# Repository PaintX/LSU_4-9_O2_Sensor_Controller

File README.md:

# LSU_4-9_O2_Sensor_Controller
Controlleur pour sonde lambda LSU 4.9 avec arduino

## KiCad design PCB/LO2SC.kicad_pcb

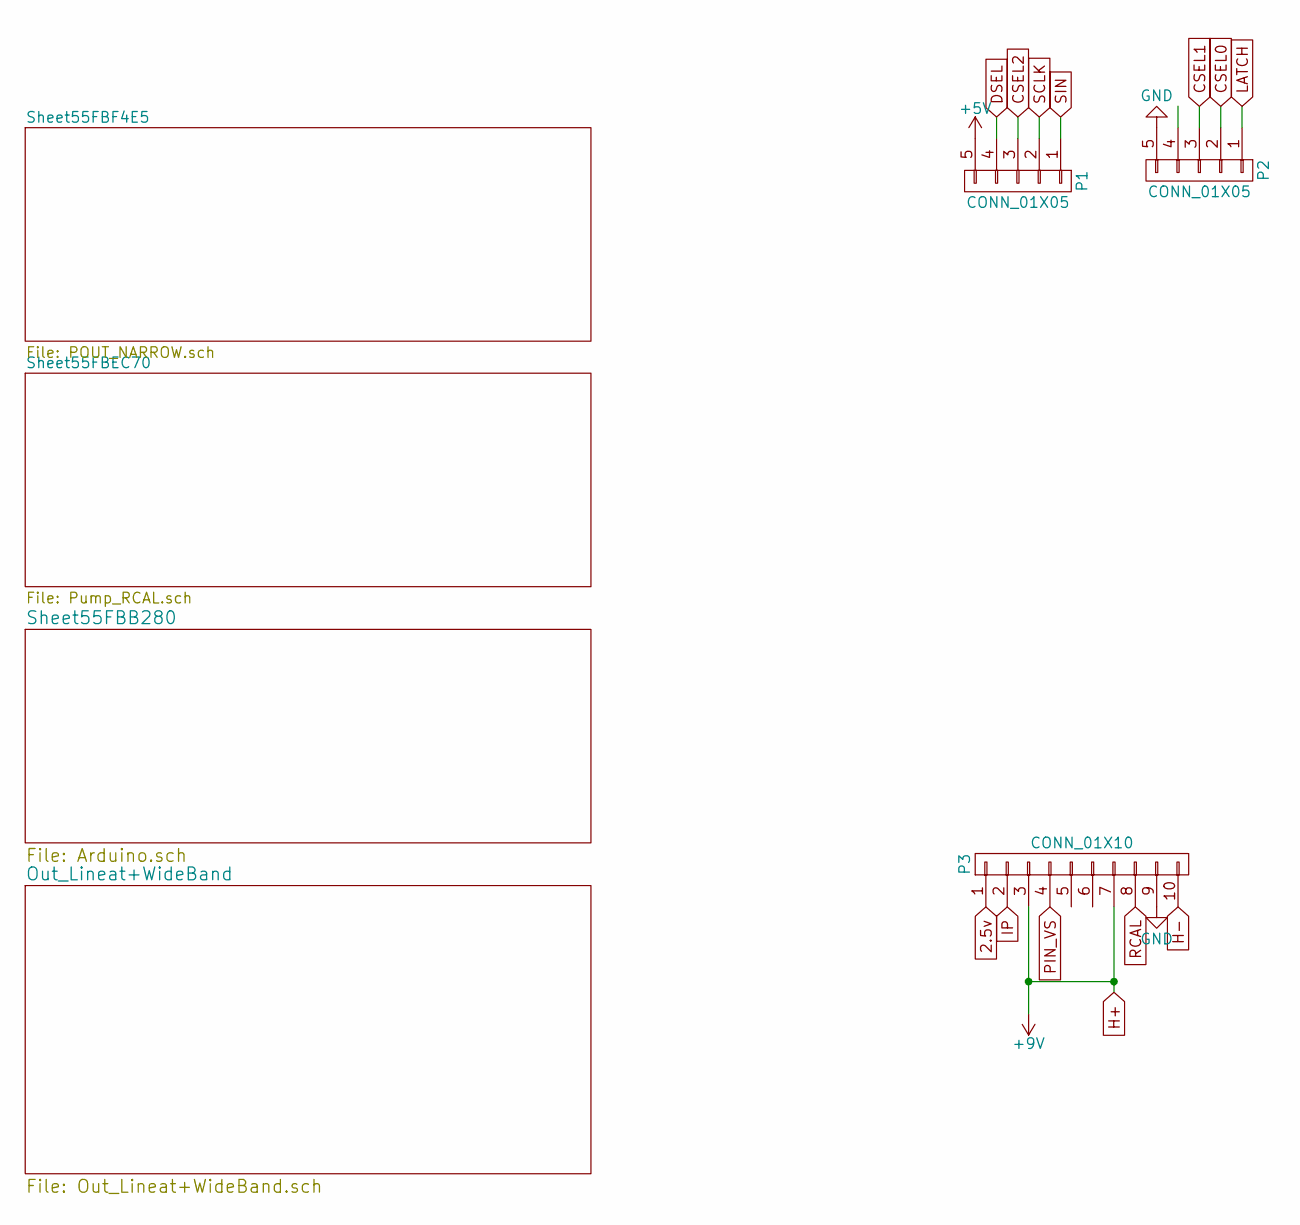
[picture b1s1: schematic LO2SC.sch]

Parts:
P1, P2: CONN_01X05; Pin_Header_Straight_1x05
P3: CONN_01X10; JAE_10Pins

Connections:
2.5v: P3.1; also elsewhere on the board
+5V: P1.5; also elsewhere on the board
CSEL0: P2.2; also elsewhere on the board
CSEL1: P2.3; also elsewhere on the board
CSEL2: P1.3; also elsewhere on the board
DSEL: P1.4; also elsewhere on the board
GND: P2.5, P3.9; also elsewhere on the board
H+: P3.3, P3.7
IP: P3.2; also elsewhere on the board
LATCH: P2.1; also elsewhere on the board
PIN_VS: P3.4; also elsewhere on the board
RCAL: P3.8; also elsewhere on the board
SCLK: P1.2; also elsewhere on the board
SIN: P1.1; also elsewhere on the board

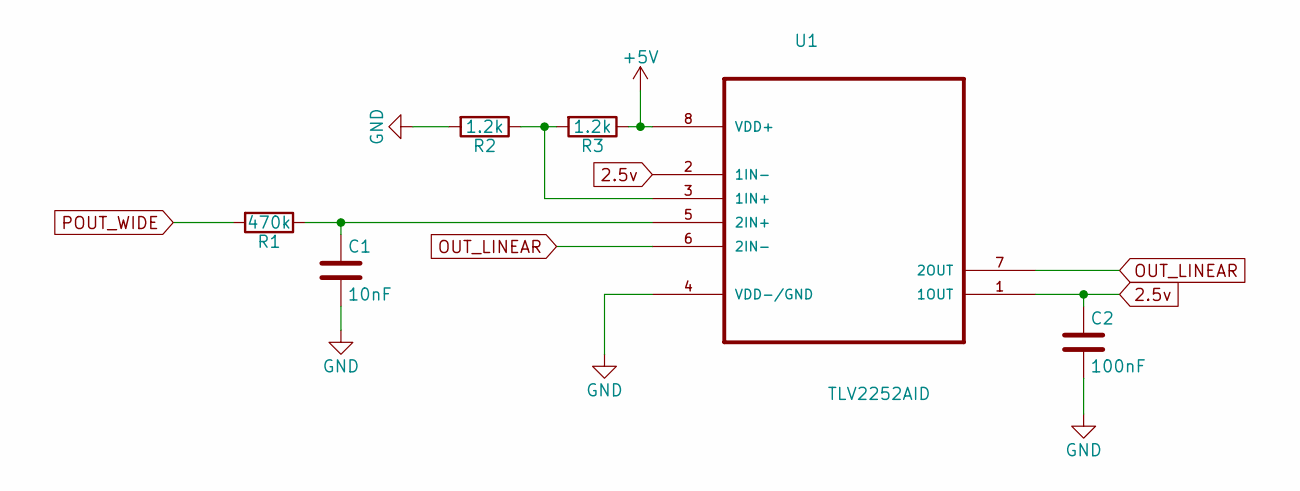
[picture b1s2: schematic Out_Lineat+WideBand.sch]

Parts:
C1: 10nF; C_0603_HandSoldering
C2: 100nF; C_0603_HandSoldering
R1: 470k; R_0603_HandSoldering
R2, R3: 1.2k; R_0603_HandSoldering
U1: TLV2252AID; SOIC127P600X175-8N

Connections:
2.5v: C2.1, U1.1 (1OUT), U1.2 (1IN-); also elsewhere on the board
+5V: R3.1, U1.8 (VDD+); also elsewhere on the board
GND: C1.2, C2.2, R2.2, U1.4 (VDD-/GND); also elsewhere on the board
unnamed: C1.1, R1.1, U1.5 (2IN+)
unnamed: R2.1, R3.2, U1.3 (1IN+)
OUT_LINEAR: U1.6 (2IN-), U1.7 (2OUT)
POUT_WIDE: R1.2; also elsewhere on the board

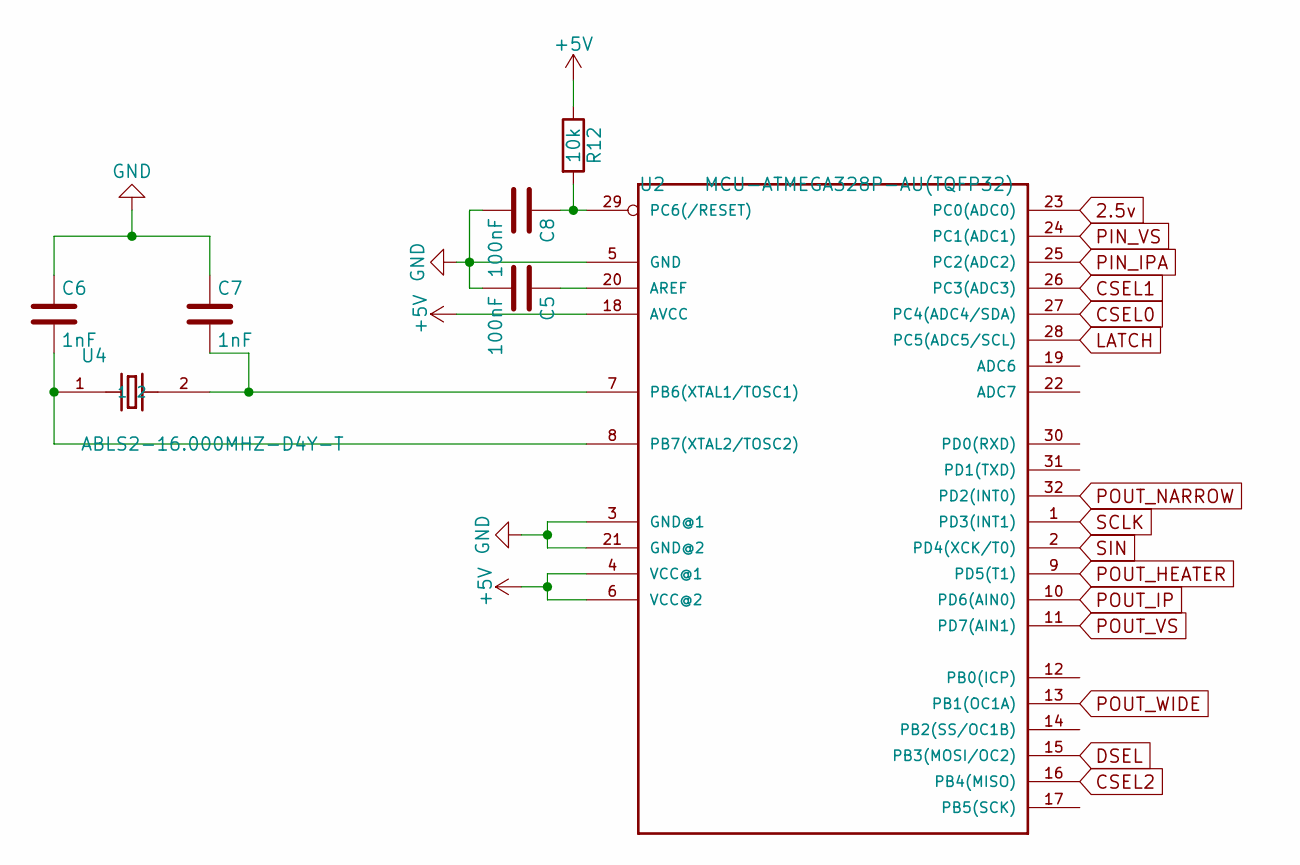
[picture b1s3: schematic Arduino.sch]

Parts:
C5, C8: 100nF; C_0603_HandSoldering
C6, C7: 1nF; C_0603_HandSoldering
R12: 10k; R_0603_HandSoldering
U2: MCU-ATMEGA328P-AU(TQFP32); TQFP32-0.8-7X7MM
U4: ABLS2-16.000MHZ-D4Y-T; HC-49

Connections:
2.5v: U2.23 (PC0(ADC0)); also elsewhere on the board
+5V: R12.1, U2.4 (VCC@1), U2.6 (VCC@2), U2.18 (AVCC); also elsewhere on the board
CSEL0: U2.27 (PC4(ADC4/SDA)); also elsewhere on the board
CSEL1: U2.26 (PC3(ADC3)); also elsewhere on the board
CSEL2: U2.16 (PB4(MISO)); also elsewhere on the board
DSEL: U2.15 (PB3(MOSI/OC2)); also elsewhere on the board
GND: C5.2, C6.1, C7.1, C8.2, U2.3 (GND@1), U2.5 (GND), U2.21 (GND@2); also elsewhere on the board
LATCH: U2.28 (PC5(ADC5/SCL)); also elsewhere on the board
unnamed: C5.1, U2.20 (AREF)
unnamed: C6.2, U2.8 (PB7(XTAL2/TOSC2)), U4.1
unnamed: C7.2, U2.7 (PB6(XTAL1/TOSC1)), U4.2
unnamed: C8.1, R12.2, U2.29 (PC6(/RESET))
PIN_IPA: U2.25 (PC2(ADC2)); also elsewhere on the board
PIN_VS: U2.24 (PC1(ADC1)); also elsewhere on the board
POUT_IP: U2.10 (PD6(AIN0)); also elsewhere on the board
POUT_NARROW: U2.32 (PD2(INT0)); also elsewhere on the board
POUT_VS: U2.11 (PD7(AIN1)); also elsewhere on the board
POUT_WIDE: U2.13 (PB1(OC1A)); also elsewhere on the board
SCLK: U2.1 (PD3(INT1)); also elsewhere on the board
SIN: U2.2 (PD4(XCK/T0)); also elsewhere on the board

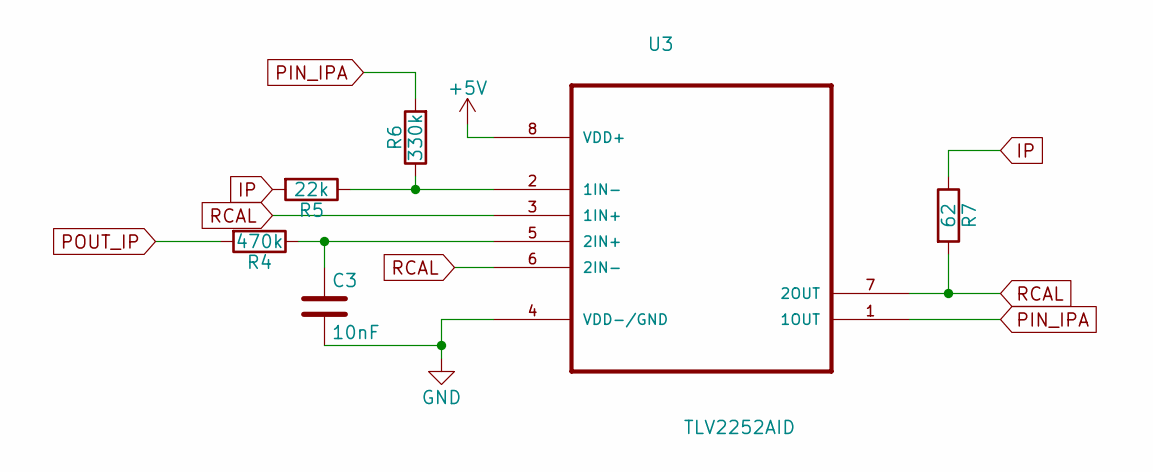
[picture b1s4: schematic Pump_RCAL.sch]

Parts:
C3: 10nF; C_0603_HandSoldering
R4: 470k; R_0603_HandSoldering
R5: 22k; R_0603_HandSoldering
R6: 330k; R_0603_HandSoldering
R7: 62; R_0603_HandSoldering
U3: TLV2252AID; SOIC127P600X175-8N

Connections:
+5V: U3.8 (VDD+); also elsewhere on the board
GND: C3.2, U3.4 (VDD-/GND); also elsewhere on the board
IP: R5.2, R7.1; also elsewhere on the board
unnamed: C3.1, R4.1, U3.5 (2IN+)
unnamed: R5.1, R6.1, U3.2 (1IN-)
PIN_IPA: R6.2, U3.1 (1OUT); also elsewhere on the board
POUT_IP: R4.2; also elsewhere on the board
RCAL: R7.2, U3.3 (1IN+), U3.6 (2IN-), U3.7 (2OUT); also elsewhere on the board

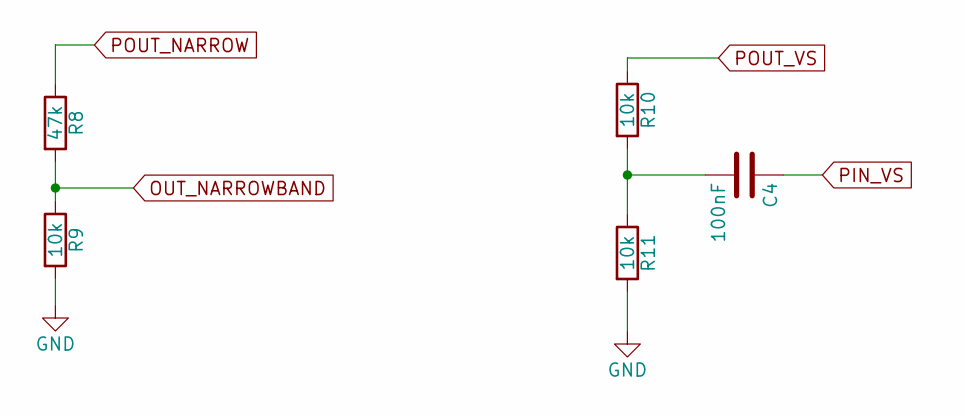
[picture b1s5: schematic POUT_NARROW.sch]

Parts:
C4: 100nF; C_0603_HandSoldering
R8: 47k; R_0603_HandSoldering
R9, R10, R11: 10k; R_0603_HandSoldering

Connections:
GND: R9.2, R11.2; also elsewhere on the board
unnamed: C4.2, R10.2, R11.1
OUT_NARROWBAND: R8.2, R9.1
PIN_VS: C4.1; also elsewhere on the board
POUT_NARROW: R8.1; also elsewhere on the board
POUT_VS: R10.1; also elsewhere on the board

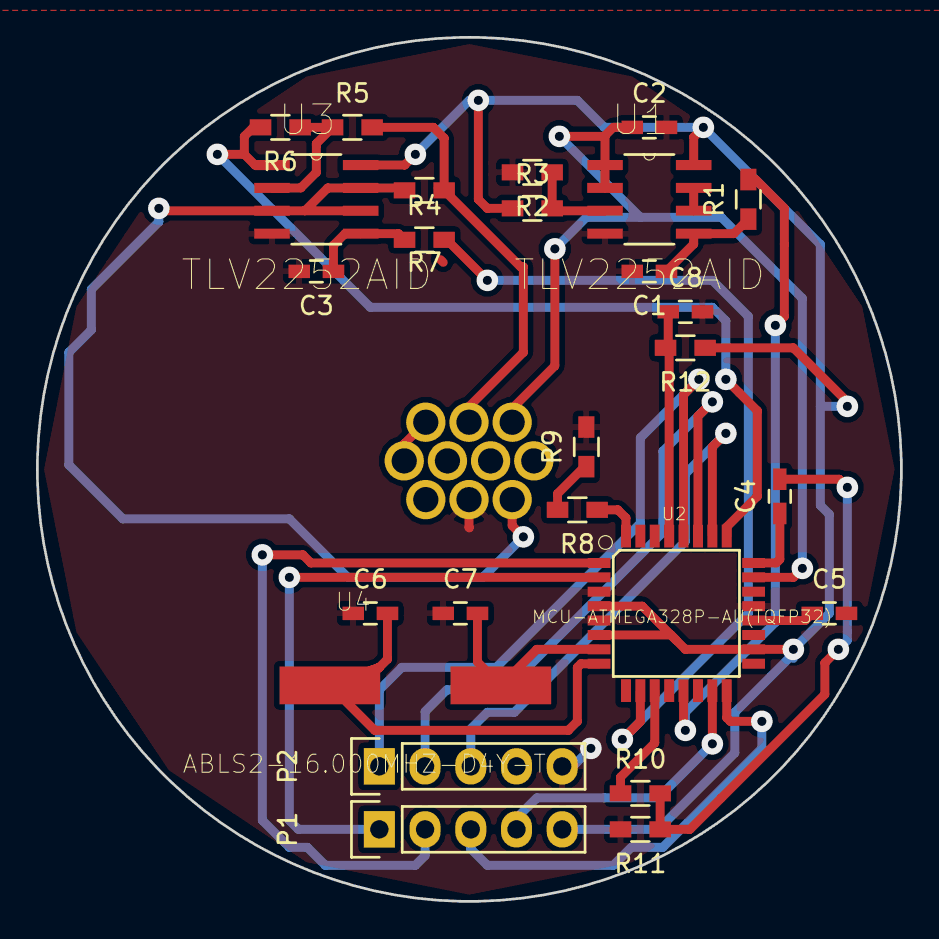
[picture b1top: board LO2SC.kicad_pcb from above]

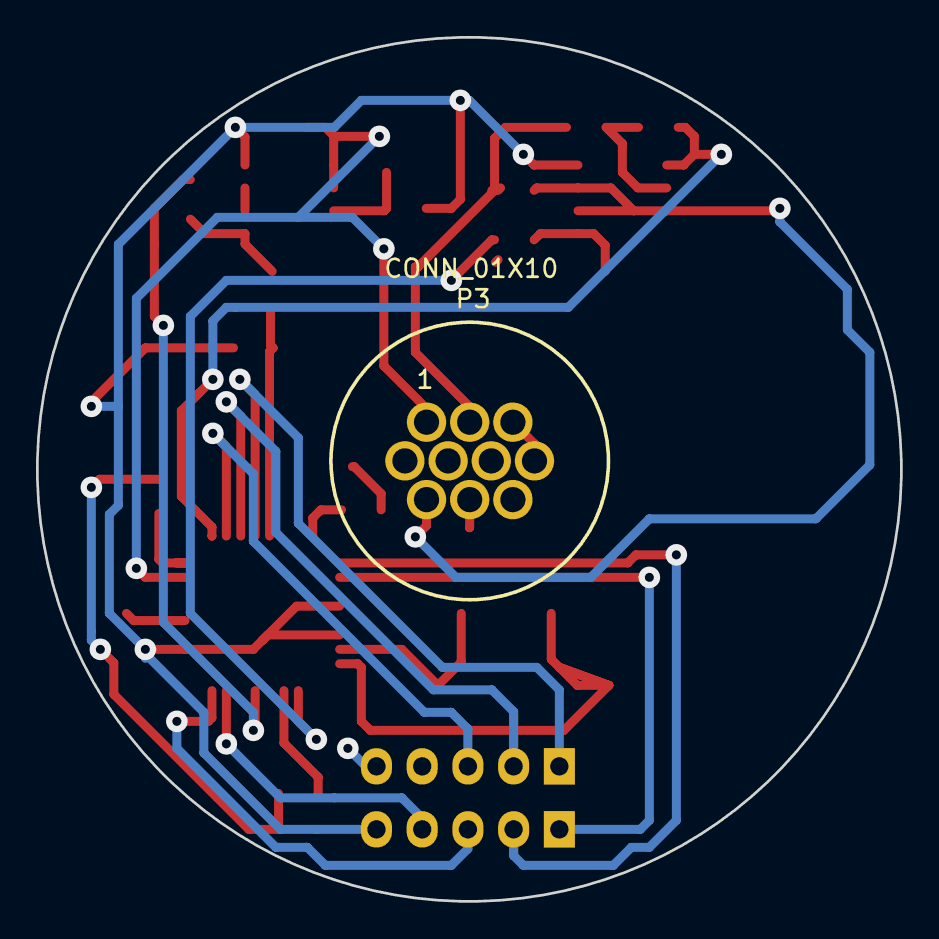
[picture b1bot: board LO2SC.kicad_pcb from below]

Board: 2 copper layers, 48.0 x 48.0 mm, 28 parts (2 on the bottom side), 30 nets.

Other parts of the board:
Ref**: Val**; vue3D

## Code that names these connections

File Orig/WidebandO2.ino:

#include <RunningAverage.h>
#include <PID_v1.h>



/*
 Some configurations
*/


#define BOARD_UNO


const float targetLambda = 1.0; // Narrowband simulation, cross point in lambda
const float widebandTop = 2.0; // Where the +5v of the linear wideband output is

const int warmUpDelay = 20000; // Initial delay we wait before starting heating of the sensor, in millis
const int initialRampUpTill = 255 / 14.0 * 7.5; // Heater warm up stage, this sets the top (TODO: Measure input voltage, max output should be 7.5v)
const int initialRampUpStep = 255 / (14.0 / 0.5); // Heater warm up stage, this is how fast the voltage ramps up per second, spec sheet says .5v a second).

double heatTarget = 2.3 / 1300.0 * 200.0; // Target voltage, this is pulse voltage divided by total target resistance, times the target cell resistance
int heatSampleTime = 500; // How often the heater is sampled for PID, in milliseconds
double pumpTarget = 0.45; // Target Nernst cell voltage
int pumpSampleTime = 40; // How often the nernst cell is sampled for PID, in milliseconds (should be slower than the RC filter feeding the opamp)

int speedOfLoop = 4; // How many millis it takes for loop to run, on Teensy++ 2.0, it's 4 millis

#define DEBUG       // DEBUG enables human readable logging and info messages
#define NO_SERIAL   // NO_SERIAL disables the CSV output of the controllers controls, a nice way to view this log is with OpenLogViewer - http://olv.diyefi.org/



/*
  Pin Definitions
*/
#if defined(BOARD_TEENSYPP20)
// Inputs
const int PIN_VGND = PIN_F0; // Analog In - Level of the virtual ground
const int PIN_VS = PIN_F1; // Analog In - Reads Nernst Cell voltage
const int PIN_IPA = PIN_F2; // Analog In - Measures pump current via differential amp

// Sensor control
const int POUT_VS = PIN_B6; // Digital Out - Pulses Nernst Cell to calculate internal resistance
const int POUT_HEATER = PIN_B5; // Analog Out - Heater control, keeps Nernst cell at right temperature
const int POUT_IP = PIN_B4; // Analog Out - Pump cell current output, keeps Nernst cell in stoich range

// Outputs
const int POUT_NARROW = PIN_D0; // Digital Out - Feeds voltage divider, 0-1v signal to ECU
const int POUT_WIDE = PIN_D1; // Analog Out - Wideband linear output



#elif defined(BOARD_UNO)
const int PIN_VGND = A0; // Analog In - Level of the virtual ground
const int PIN_VS = A1; // Analog In - Reads Nernst Cell voltage
const int PIN_IPA = A2; // Analog In - Measures pump current via differential amp

// Sensor control
const int POUT_VS = 7; // Digital Out - Pulses Nernst Cell to calculate internal resistance
const int POUT_HEATER = 5; // Analog Out - Heater control, keeps Nernst cell at right temperature
const int POUT_IP = 6; // Analog Out - Pump cell current output, keeps Nernst cell in stoich range

// Outputs
const int POUT_NARROW = 2; // Digital Out - Feeds voltage divider, 0-1v signal to ECU
const int POUT_WIDE = 9; // Analog Out - Wideband linear output



#else
#error "No board defined"
#endif

/*
  Start of code
*/
#ifdef DEBUG
#define DP(...) Serial.print(__VA_ARGS__)
#define DPL(...) Serial.println(__VA_ARGS__)
#else
#define DP(...)
#define DPL(...)
#endif



double heatIn, heatOut;
PID heater(&heatIn, &heatOut, &heatTarget, 800, 100, 1, REVERSE);
double pumpIn, pumpOut;
PID pump(&pumpIn, &pumpOut, &pumpTarget, 800, 100, 0.001, DIRECT);

RunningAverage vgndavg(1);
RunningAverage ipaavg(pumpSampleTime/speedOfLoop*5);
RunningAverage nernstavg(pumpSampleTime/speedOfLoop);

float volts(int adc) {
  return adc / 1024.0 * 5.0;
}

float vGndVolts() {
  vgndavg.addValue(volts(analogRead(PIN_VGND)));
  return vgndavg.getAverage();
}

float nernstVolts() {
  nernstavg.addValue(volts(analogRead(PIN_VS)));
  return nernstavg.getAverage();
}

float pumpVolts() {
  ipaavg.addValue(volts(analogRead(PIN_IPA)));
  return ipaavg.getAverage();
}

float nernstResistanceVolts() {
    int before = analogRead(PIN_VS); // Read nernst before pulse
    digitalWrite(POUT_VS, 1); // Pulse it
    delayMicroseconds(30); // Wait for the pulse cap to reach full voltage
    int after = analogRead(PIN_VS); // Read during the pulse
    digitalWrite(POUT_VS, 0); // Restore it
    delayMicroseconds(200); // Give the nernst cell and cap some time to equalise back out after
    return volts(after - before);
}

#define LAMBDA_LOOKUP_SIZE 20
const float lambdaLookup[LAMBDA_LOOKUP_SIZE] = {
  -2.22, 0.65,
  -1.82, 0.70,
  -1.11, 0.80,
  -0.50, 0.90,
   0.00, 1.016,
   0.33, 1.18,
   0.67, 1.43,
   0.94, 1.70,
   1.38, 2.42,
   2.54, 4.99
};

float lambda(float amps) {
  if (amps < lambdaLookup[0]) return 0.0; // Too rich for sensor
  if (amps > lambdaLookup[LAMBDA_LOOKUP_SIZE-2]) return 9.99; // To lean to care
  for (int x = 0; x < LAMBDA_LOOKUP_SIZE-2; x = x + 2) {
    if (amps >= lambdaLookup[x] && amps <= lambdaLookup[x+2]) {
      // Interpolate the lookup
      return (amps - lambdaLookup[x]) / (lambdaLookup[x+2] - lambdaLookup[x]) * (lambdaLookup[x+3] - lambdaLookup[x+1]) + lambdaLookup[x+1];
    }
  }
}

void serialHeader() {
  #ifndef NO_SERIAL
  Serial.println("millis,lambda,ipa,vgnd,heatIn,heatOut,heatTarget,pumpIn,pumpOut,pumpTarget");
  #endif
}

void serialLog(float l, float ipa, float vgnd) {
  // lambda, ipa, vgnd, heatIn, heatOut, heatTarget, pumpIn, pumpOut, pumpTarget
  #ifndef DEBUG
  #ifndef NO_SERIAL
    Serial.print(millis());
    Serial.print(",");
    Serial.print(l);
    Serial.print(",");
    Serial.print(ipa);
    Serial.print(",");
    Serial.print(vgnd);
    Serial.print(",");
    Serial.print(heatIn);
    Serial.print(",");
    Serial.print(heatOut);
    Serial.print(",");
    Serial.print(heatTarget);
    Serial.print(",");
    Serial.print(pumpIn);
    Serial.print(",");
    Serial.print(pumpOut);
    Serial.print(",");
    Serial.print(pumpTarget);
    Serial.println("");
  #endif
  #endif
}

void setup() {
  // Configure pins
  pinMode(PIN_VS, INPUT);
  pinMode(PIN_IPA, INPUT);
  pinMode(PIN_VGND, INPUT);
  
  pinMode(POUT_NARROW, OUTPUT);
  digitalWrite(POUT_NARROW, 0);
  
  pinMode(POUT_WIDE, OUTPUT);
  analogWrite(POUT_WIDE, 0);
  
  pinMode(POUT_VS, OUTPUT);
  digitalWrite(POUT_VS, 0);
  
  pinMode(POUT_IP, OUTPUT);
  analogWrite(POUT_IP, 128);
  
  pinMode(POUT_HEATER, OUTPUT);
  analogWrite(POUT_HEATER, 0);
  
  // Configure PIDs
  heater.SetOutputLimits(0, initialRampUpTill);
  heater.SetSampleTime(heatSampleTime);
  heater.SetMode(AUTOMATIC);
  pump.SetOutputLimits(0, 250);
  pump.SetSampleTime(pumpSampleTime);
  pump.SetMode(AUTOMATIC);
  
  // Start running
  Serial.begin(115200);
  delay(1000);
  Serial.println();
  Serial.println();
  Serial.println();
  Serial.println();
  serialHeader();
  
  DPL("Hello Master!");
  
  DPL("Performing delay prior to warmup");
  delay(warmUpDelay); // Wait for some warm gasses through the exhaust
  
  // Slowly ramp up the sensors heater
  DPL("Warming up!");
  heatOut = 0;
  while (heatOut < initialRampUpTill) {
    if ((heatIn = nernstResistanceVolts()) < heatTarget) break; // Temperature is at target already, break out early to let PID take over
    heatOut += initialRampUpStep;
    analogWrite(POUT_HEATER, heatOut);
    serialLog(0.0,0.0,0.0);
    delay(1000);
  }
  DPL("Warm up complete");
}

#ifdef DEBUG
int debug;
#endif
void loop() {

  heatIn = nernstResistanceVolts();
  heater.Compute();
  analogWrite(POUT_HEATER, heatOut);
  
  float vgnd = vGndVolts();
  
  pumpIn = nernstVolts() - vgnd;
  pump.Compute();
  analogWrite(POUT_IP, pumpOut);
  
  // We rely on the circuit to give us a good range of mA to V, for a 61.9 ohm sense resistor, you need a 1 to 14.5395 ratio on the opamp, 22k and 330k across it gives a good result
  float ipa =  pumpVolts() - vgnd;
  float l = lambda(ipa);
  if (l > targetLambda) {
    digitalWrite(POUT_NARROW, 0); // Lean
  } else {
    digitalWrite(POUT_NARROW, 1); // Rich
  }
  
  unsigned int widebandOut;
  if (l < 0.65) widebandOut = 0;
  else if (l > widebandTop) widebandOut = 255;
  else widebandOut = ((l / widebandTop) - (0.65 / widebandTop)) * 255;
  analogWrite(POUT_WIDE, widebandOut);
  
  
  serialLog(l, ipa, vgnd);
  #ifdef DEBUG
  if (debug++ >= 500) {
    DP("Heater: Volts: "); DP(heatIn); DP(" Target: "); DP(heatTarget); DP(" Out: "); DPL(heatOut);
    DP("Nernst: Volts: "); DP(pumpIn); DP(" Target: "); DP(pumpTarget); DP(" Out: "); DPL(pumpOut);
    DP("VGnd: "); DP(vgnd); DP(" IpA: "); DP(ipa); DP(" Lambda: "); DPL(lambda(ipa));
    debug = 0;
  }
  #endif
}

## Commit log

2015-09-17 - creation fichier README.md
    - creation fichier README.md
2015-09-17 - ajout fichier original pour tensy ++ 2.0
2015-09-17 - Debut de schematique
2015-09-18 - ajout de schematiques
2015-09-21 - premier test avec l'arduino
2015-09-22 - routage
2015-09-24 - routage en cours
